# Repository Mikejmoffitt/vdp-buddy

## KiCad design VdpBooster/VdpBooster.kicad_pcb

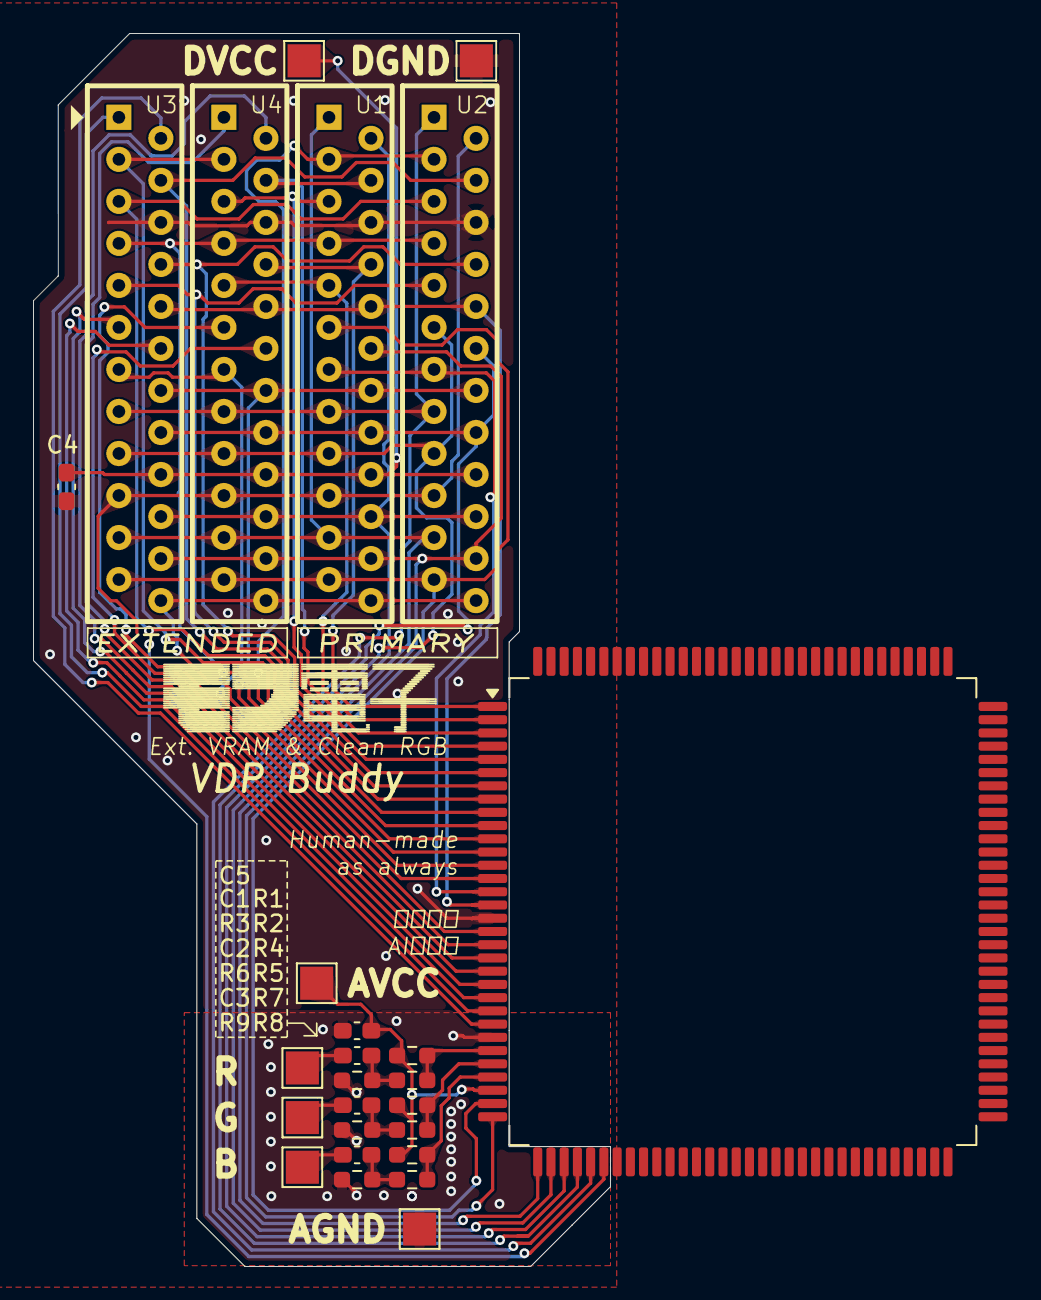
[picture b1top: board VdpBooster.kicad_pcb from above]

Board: 2 copper layers, 34.9 x 74.5 mm, 26 parts (0 on the bottom side), 45 nets.

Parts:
C1, C2, C3: 22nF; C_0603_1608Metric_Pad1.08x0.95mm_HandSolder
C4: 0.1uF; C_0603_1608Metric_Pad1.08x0.95mm_HandSolder
C5: 1.0uF; C_0603_1608Metric_Pad1.08x0.95mm_HandSolder
R1, R4, R7: 5.6k; R_0603_1608Metric_Pad0.98x0.95mm_HandSolder
R2, R5, R8: 4.7k; R_0603_1608Metric_Pad0.98x0.95mm_HandSolder
R3, R6, R9: 1.2k; R_0603_1608Metric_Pad0.98x0.95mm_HandSolder
TP1, TP2, TP3, TP4, TP5, TP6, TP7: TestPoint; TestPoint_Pad_2.0x2.0mm
U1, U2, U3, U4: M5M4C264L; ZIP-24
U5: 315-5313A; PQFP-128_28x28mm_P0.8mm

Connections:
/A0: U1.11 (W0/IO0), U1.23 (A0), U2.23 (A0), U3.23 (A0), U4.23 (A0), U5.31 (AD0)
/A1: U1.12 (W1/IO1), U1.22 (A1), U2.22 (A1), U3.22 (A1), U4.22 (A1), U5.32 (AD1)
/A2: U1.1 (W2/IO2), U1.21 (A2), U2.21 (A2), U3.21 (A2), U4.21 (A2), U5.33 (AD2)
/A3: U1.2 (W3/IO3), U1.20 (A3), U2.20 (A3), U3.20 (A3), U4.20 (A3), U5.34 (AD3)
/A4: U1.17 (A4), U2.11 (W0/IO0), U2.17 (A4), U3.17 (A4), U4.17 (A4), U5.35 (AD4)
/A5: U1.16 (A6), U2.12 (W1/IO1), U2.16 (A6), U3.16 (A6), U4.16 (A6), U5.36 (AD5)
/A6: U1.15 (A5), U2.1 (W2/IO2), U2.15 (A5), U3.15 (A5), U4.15 (A5), U5.37 (AD6)
/A7: U1.19 (A7), U2.2 (W3/IO3), U2.19 (A7), U3.19 (A7), U4.19 (A7), U5.38 (AD7)
/RD0: U4.11 (W0/IO0), U5.18 (RD0)
/RD1: U4.12 (W1/IO1), U5.19 (RD1)
/RD2: U4.1 (W2/IO2), U5.20 (RD2)
/RD3: U4.2 (W3/IO3), U5.21 (RD3)
/RD4: U3.11 (W0/IO0), U5.22 (RD4)
/RD5: U3.12 (W1/IO1), U5.23 (RD5)
/RD6: U3.1 (W2/IO2), U5.24 (RD6)
/RD7: U3.2 (W3/IO3), U5.25 (RD7)
/SC: U1.7 (SC), U2.7 (SC), U3.7 (SC), U4.7 (SC), U5.11 (SC)
/SD0: U1.8 (SIO0), U4.8 (SIO0), U5.1 (SD0)
/SD1: U1.9 (SIO1), U4.9 (SIO1), U5.2 (SD1)
/SD2: U1.4 (SIO2), U4.4 (SIO2), U5.3 (SD2)
/SD3: U1.5 (SIO3), U4.5 (SIO3), U5.4 (SD3)
/SD4: U2.8 (SIO0), U3.8 (SIO0), U5.5 (SD4)
/SD5: U2.9 (SIO1), U3.9 (SIO1), U5.6 (SD5)
/SD6: U2.4 (SIO2), U3.4 (SIO2), U5.7 (SD6)
/SD7: U2.5 (SIO3), U3.5 (SIO3), U5.8 (SD7)
/VID_B: R7.2, R8.1, U5.29 (B)
/VID_B_ENC: C3.2, TP7.1 (1_1)
/VID_G: R4.2, R5.1, U5.28 (G)
/VID_G_ENC: C2.2, TP6.1 (1_1)
/VID_R: R1.2, R2.1, U5.27 (R)
/VID_R_ENC: C1.2, TP5.1 (1_1)
/~CAS1: U1.24 (~CAS), U2.24 (~CAS), U3.24 (~CAS), U4.24 (~CAS), U5.13 (~CAS1)
/~OE1: U1.10 (~DT/~OE), U2.10 (~DT/~OE), U3.10 (~DT/~OE), U4.10 (~DT/~OE), U5.16 (~OE1)
/~RAS1: U1.14 (~RAS), U2.14 (~RAS), U3.14 (~RAS), U4.14 (~RAS), U5.12 (~RAS1)
/~SE0: U1.3 (~SE), U2.3 (~SE), U5.10 (~SE0)
/~SE1: U3.3 (~SE), U4.3 (~SE), U5.9 (~SE1)
/~WE0: U1.13 (~WB/~WE), U2.13 (~WB/~WE), U5.15 (~WE0)
/~WE1: U3.13 (~WB/~WE), U4.13 (~WB/~WE), U5.14 (~WE1)
GND: C4.2, TP4.1 (1_1), U1.6 (GND), U2.6 (GND), U3.6 (GND), U4.6 (GND), U5.17 (GND)
GNDA: C5.2, R3.1, R6.1, R9.1, TP2.1 (1_1), U5.26 (AGC)
unnamed: C1.1, R2.2, R3.2
unnamed: C2.1, R5.2, R6.2
unnamed: C3.1, R8.2, R9.2
VCC: C4.1, TP3.1 (1_1), U1.18 (VCC), U2.18 (VCC), U3.18 (VCC), U4.18 (VCC)
VCCA: C5.1, R1.1, R4.1, R7.1, TP1.1 (1_1), U5.30 (AVC)
